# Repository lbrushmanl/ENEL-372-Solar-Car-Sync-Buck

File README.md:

# ENEL-372-Solar-Car-Sync-Buck
This project involved making a buck converter that would be used to power a small solar-powered RC car. 

Image of my Synchronous converter

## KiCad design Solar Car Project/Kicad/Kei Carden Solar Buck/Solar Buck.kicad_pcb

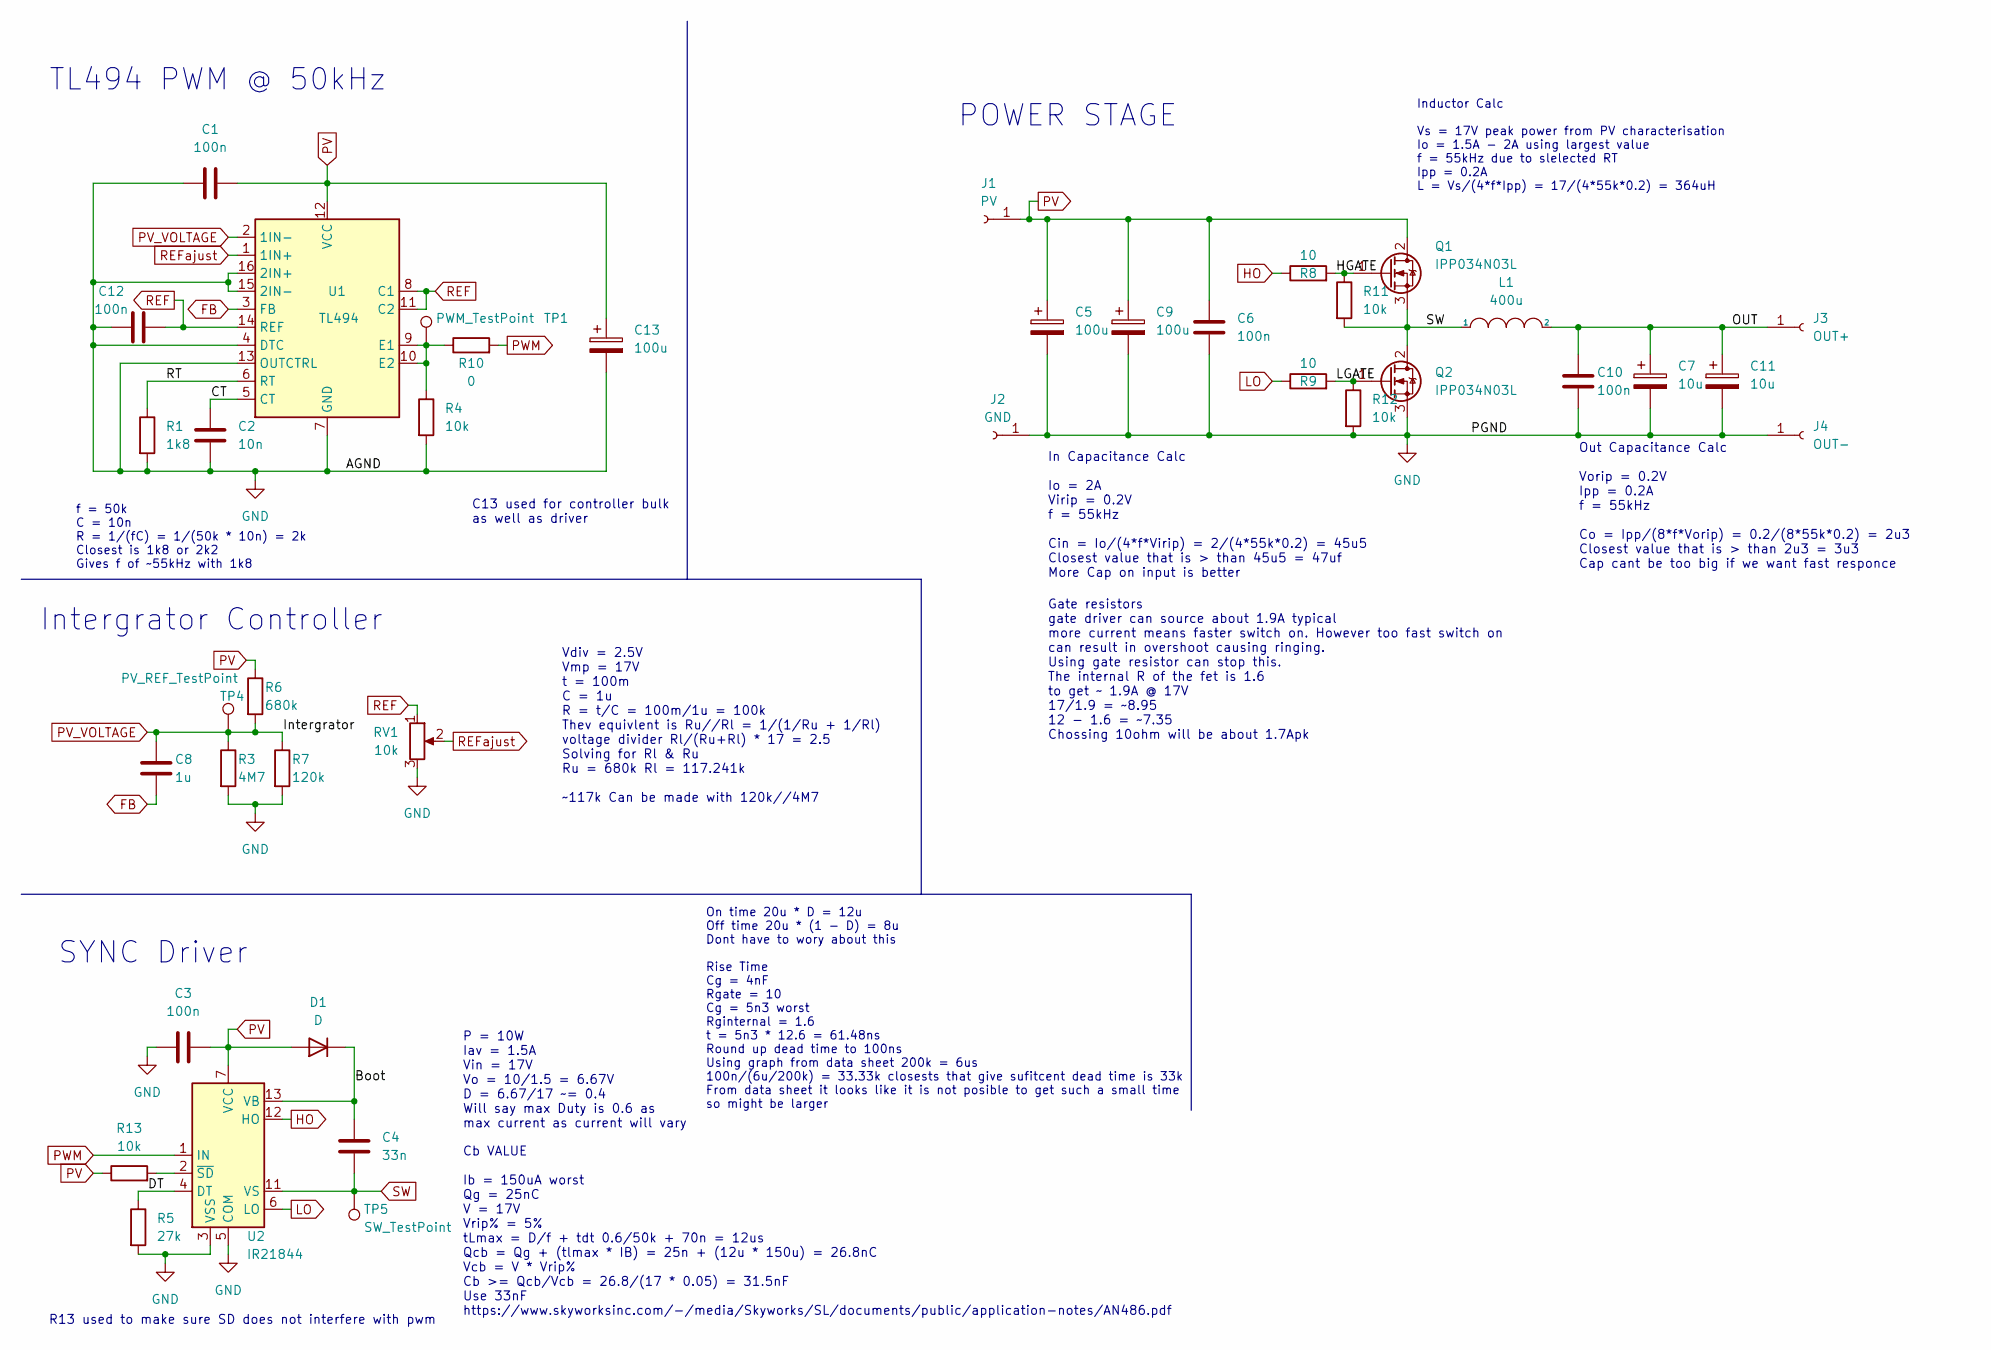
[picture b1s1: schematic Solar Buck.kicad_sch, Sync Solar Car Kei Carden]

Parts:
C1, C3, C6, C10, C12: 100n; C_Disc_D3.4mm_W2.1mm_P2.50mm
C2: 10n; C_Rect_L7.0mm_W2.5mm_P5.00mm
C4: 33n; C_Rect_L7.0mm_W2.5mm_P5.00mm
C5: 100u; CP_Radial_D8.0mm_P5.00mm
C7, C11: 10u; CP_Radial_D5.0mm_P2.50mm
C8: 1u; C_Rect_L7.0mm_W4.5mm_P5.00mm
C9, C13: 100u; CP_Radial_D5.0mm_P2.50mm
D1: D; D_A-405_P12.70mm_Horizontal
J1: PV; Spade-Terminal
J2: GND; Spade-Terminal
J3: OUT+; Spade-Terminal
J4: OUT-; Spade-Terminal
L1: 400u; RM8 Former
Q1, Q2: IPP034N03L; TO-220-3_Vertical
R1: 1k8; R_Axial_DIN0207_L6.3mm_D2.5mm_P7.62mm_Horizontal
R3: 4M7; R_Axial_DIN0207_L6.3mm_D2.5mm_P7.62mm_Horizontal
R4, R13: 10k; R_Axial_DIN0207_L6.3mm_D2.5mm_P7.62mm_Horizontal
R5: 27k; R_Axial_DIN0207_L6.3mm_D2.5mm_P7.62mm_Horizontal
R6: 680k; R_Axial_DIN0207_L6.3mm_D2.5mm_P7.62mm_Horizontal
R7: 120k; R_Axial_DIN0207_L6.3mm_D2.5mm_P7.62mm_Horizontal
R8: 10; R_Axial_DIN0207_L6.3mm_D2.5mm_P2.54mm_Vertical
R9: 10; R_Axial_DIN0207_L6.3mm_D2.5mm_P7.62mm_Horizontal
R10: 0; R_Axial_DIN0207_L6.3mm_D2.5mm_P7.62mm_Horizontal
R11, R12: 10k; R_Axial_DIN0207_L6.3mm_D2.5mm_P2.54mm_Vertical
RV1: 10k; Potentiometer_Bourns_3296W_Vertical
TP1: PWM_TestPoint; TestPoint_Pad_D1.0mm
TP4: PV_REF_TestPoint; TestPoint_Pad_D1.0mm
TP5: SW_TestPoint; TestPoint_Pad_D1.0mm
U1: TL494; DIP-16_W7.62mm_Socket_LongPads
U2: IR21844; DIP-14_W7.62mm_Socket_LongPads

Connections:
/Boot: C4.1, D1.1 (K), U2.13 (VB)
/CT: C2.1, U1.5 (CT)
/DT: R5.1, U2.4 (DT)
/HGATE: Q1.1 (G), R8.2, R11.1
/LGATE: Q2.1 (G), R9.2, R12.1
/OUT: C7.1, C10.1, C11.1, J3.1, L1.2
/RT: R1.1, U1.6 (RT)
FB: C8.2, U1.3 (FB)
GND: C1.1, C2.2, C3.1, C5.2, C6.2, C7.2, C9.2, C10.2, C11.2, C12.1, C13.2, J2.1, J4.1, Q2.3 (S), R1.2, R3.2, R4.2, R5.2, R7.2, R12.2, RV1.3, U1.4 (DTC), U1.7 (GND), U1.13 (OUTCTRL), U1.15 (2IN-), U1.16 (2IN+), U2.3 (VSS), U2.5 (COM)
HO: R8.1, U2.12 (HO)
LO: R9.1, U2.6 (LO)
unnamed: R4.1, R10.1, TP1.1, U1.9 (E1), U1.10 (E2)
unnamed: R13.2, U2.2 (~SD)
PV: C1.2, C3.2, C5.1, C6.1, C9.1, C13.1, D1.2 (A), J1.1, Q1.2 (D), R6.1, R13.1, U1.12 (VCC), U2.7 (VCC)
PV_VOLTAGE: C8.1, R3.1, R6.2, R7.1, TP4.1, U1.2 (1IN-); also elsewhere on the board
PWM: R10.2, U2.1 (IN)
REF: C12.2, RV1.1, U1.8 (C1), U1.11 (C2), U1.14 (REF)
REFajust: RV1.2, U1.1 (1IN+)
SW: C4.2, L1.1, Q1.3 (S), Q2.2 (D), R11.2, TP5.1, U2.11 (VS)

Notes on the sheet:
C13 used for controller bulk as well as driver
POWER STAGE
Intergrator Controller
P = 10W Iav = 1.5A Vin = 17V Vo = 10/1.5 = 6.67V D = 6.67/17 ~= 0.4 Will say max Duty is 0.6 as max current as current will vary
Out Capacitance Calc Vorip = 0.2V Ipp = 0.2A f = 55kHz Co = Ipp/(8*f*Vorip) = 0.2/(8*55k*0.2) = 2u3 Closest value that is > than 2u3 = 3u3 Cap cant be too big if we want fast responce
In Capacitance Calc Io = 2A Virip = 0.2V f = 55kHz Cin = Io/(4*f*Virip) = 2/(4*55k*0.2) = 45u5 Closest value that is > than 45u5 = 47uf More Cap on input is better
f = 50k C = 10n R = 1/(fC) = 1/(50k * 10n) = 2k Closest is 1k8 or 2k2 Gives f of ~55kHz with 1k8
R13 used to make sure SD does not interfere with pwm
Gate resistors gate driver can source about 1.9A typical more current means faster switch on. However too fast switch on can result in overshoot causing ringing. Using gate resistor can stop this. The internal R of the fet is 1.6 to get ~ 1.9A @ 17V 17/1.9 = ~8.95 12 - 1.6 = ~7.35 Chossing 10ohm wi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
Vdiv = 2.5V Vmp = 17V t = 100m C = 1u R = t/C = 100m/1u = 100k Thev equivlent is Ru//Rl = 1/(1/Ru + 1/Rl) voltage divider Rl/(Ru+Rl) * 17 = 2.5 Solving for Rl & Ru Ru = 680k Rl = 117.241k ~117k Can be made with 120k//4M7
TL494 PWM @ 50kHz
SYNC Driver
On time 20u * D = 12u Off time 20u * (1 - D) = 8u Dont have to wory about this Rise Time Cg = 4nF Rgate = 10 Cg = 5n3 worst Rginternal = 1.6 t = 5n3 * 12.6 = 61.48ns Round up dead time to 100ns Using graph from data sheet 200k = 6us 100n/(6u/200k) = 33.33k closests that give sufitcent dead time is 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
Inductor Calc Vs = 17V peak power from PV characterisation Io = 1.5A - 2A using largest value f = 55kHz due to slelected RT Ipp = 0.2A L = Vs/(4*f*Ipp) = 17/(4*55k*0.2) = 364uH
Cb VALUE Ib = 150uA worst Qg = 25nC V = 17V Vrip% = 5% tLmax = D/f + tdt 0.6/50k + 70n = 12us Qcb = Qg + (tlmax * IB) = 25n + (12u * 150u) = 26.8nC Vcb = V * Vrip% Cb >= Qcb/Vcb = 26.8/(17 * 0.05) = 31.5nF Use 33nF https://www.skyworksinc.com/-/media/Skyworks/SL/documents/public/application-notes/A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

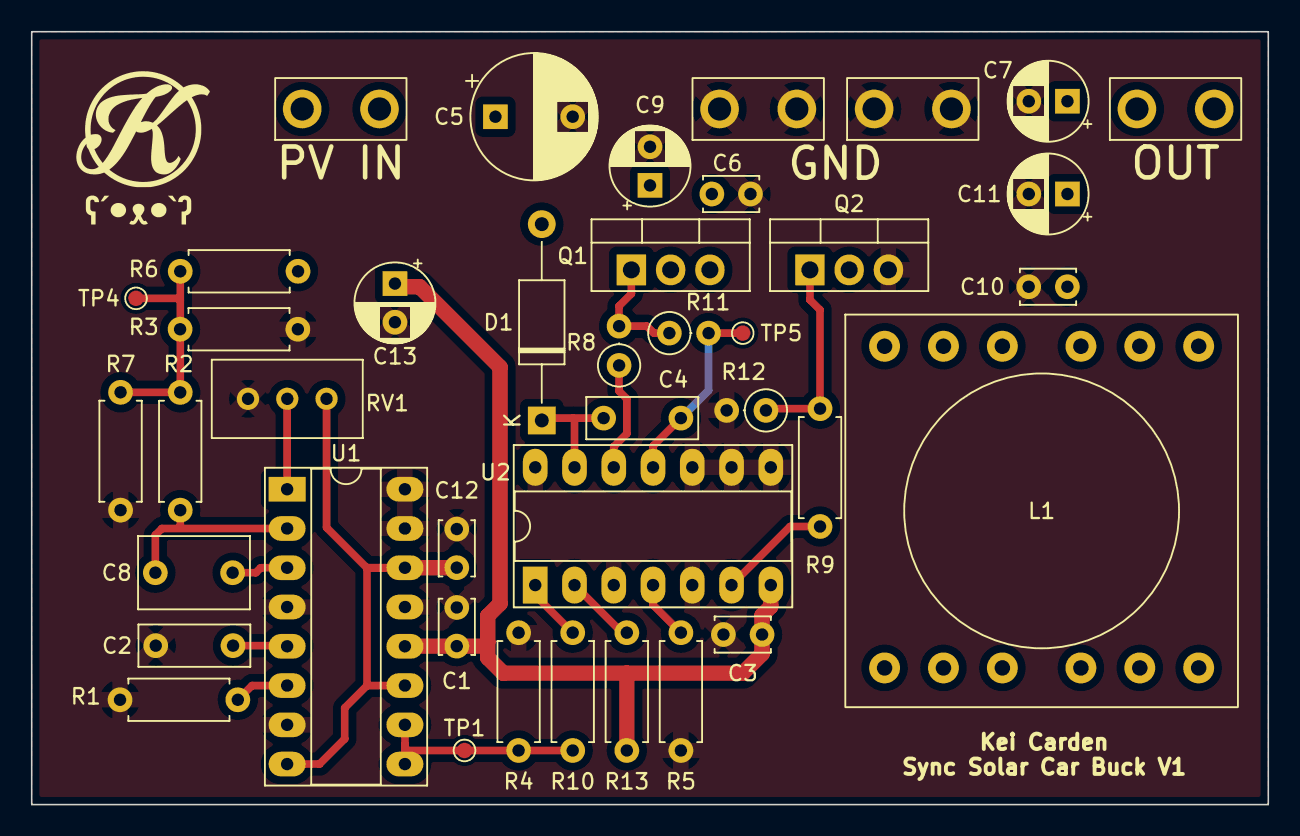
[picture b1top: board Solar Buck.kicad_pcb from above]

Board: 2 copper layers, 80.0 x 50.0 mm, 40 parts (0 on the bottom side), 19 nets.

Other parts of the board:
R2: 100k; R_Axial_DIN0207_L6.3mm_D2.5mm_P7.62mm_Horizontal

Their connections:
PV_VOLTAGE: R2.1; also elsewhere on the board

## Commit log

2022-11-30 Add solar car project
